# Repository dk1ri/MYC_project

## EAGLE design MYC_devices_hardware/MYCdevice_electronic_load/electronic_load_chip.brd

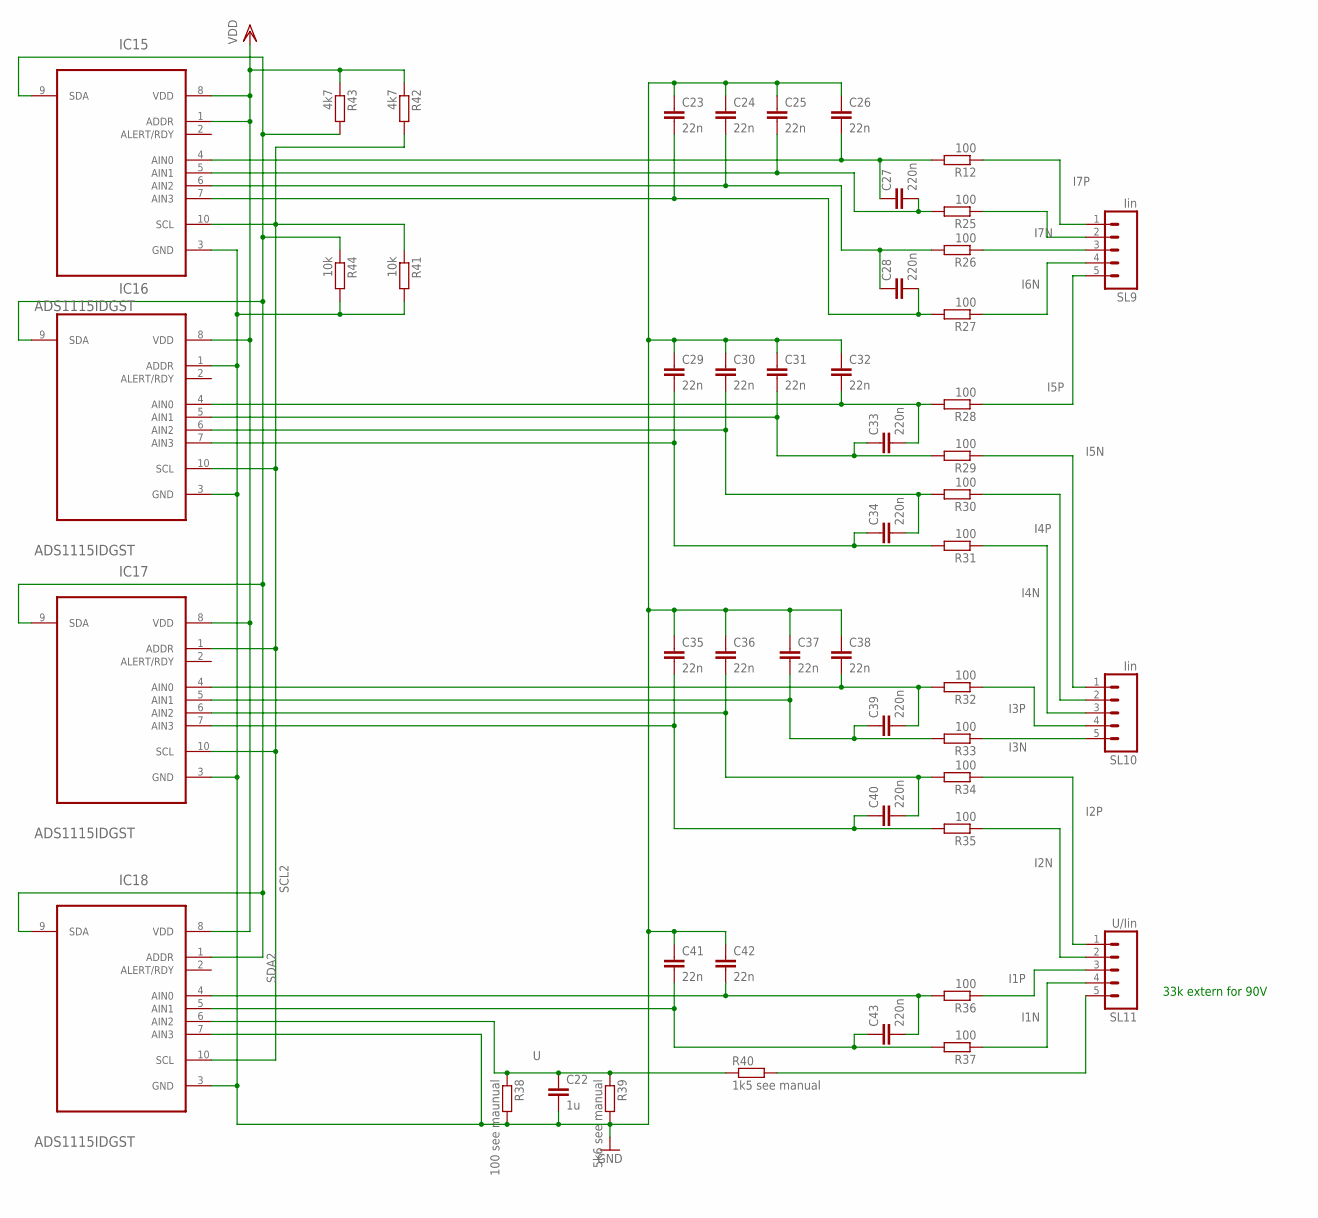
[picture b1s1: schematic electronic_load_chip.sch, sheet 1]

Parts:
C22: 1u; C1206
C23, C24, C25, C26, C29, C30, C31, C32, C35, C36, C37, C38, C41, C42: 22n; C1206
C27, C28, C33, C34, C39, C40, C43: 220n; C1206
IC15, IC16, IC17, IC18: ADS1115IDGST; SOP50P490X110-10N
R12, R25, R26, R27, R28, R29, R30, R31, R32, R33, R34, R35, R36, R37: 100; R1206
R38: 100 see maunual; R1206
R39: 5k6 see manual; R1206
R40: 1k5 see manual; R1206
R41, R44: 10k; R1206
R42, R43: 4k7; R1206
SL9, SL10: Iin; 05P
SL11: U/Iin; 05P

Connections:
GND: C22.2, C23.1, C24.1, C25.1, C26.1, C29.1, C30.1, C31.1, C32.1, C35.1, C36.1, C37.1, C38.1, C41.1, C42.1, IC15.3 (GND), IC16.1 (ADDR), IC16.3 (GND), IC17.3 (GND), IC18.3 (GND), IC18.7 (AIN3), R38.2, R39.2, R41.2, R44.2; also elsewhere on the board
I1N: R37.1, SL11.4
I1P: R36.1, SL11.3
I2N: R35.1, SL11.2
I2P: R34.1, SL11.1
I3N: R33.1, SL10.5
I3P: R32.1, SL10.4
I4N: R31.1, SL10.3
I4P: R30.1, SL10.2
I5N: R29.1, SL10.1
I5P: R28.1, SL9.5
I6N: R27.1, SL9.4
I6P: R26.1, SL9.3
I7N: R25.1, SL9.2
I7P: R12.1, SL9.1
unnamed: C26.2, C27.1, IC15.4 (AIN0), R12.2
unnamed: C32.2, C33.2, IC16.4 (AIN0), R28.2
unnamed: R40.2, SL11.5
unnamed: C31.2, C33.1, IC16.5 (AIN1), R29.2
unnamed: C30.2, C34.2, IC16.6 (AIN2), R30.2
unnamed: C29.2, C34.1, IC16.7 (AIN3), R31.2
unnamed: C38.2, C39.2, IC17.4 (AIN0), R32.2
unnamed: C37.2, C39.1, IC17.5 (AIN1), R33.2
unnamed: C36.2, C40.2, IC17.6 (AIN2), R34.2
unnamed: C24.2, C28.1, IC15.6 (AIN2), R26.2
unnamed: C25.2, C27.2, IC15.5 (AIN1), R25.2
unnamed: C35.2, C40.1, IC17.7 (AIN3), R35.2
unnamed: C23.2, C28.2, IC15.7 (AIN3), R27.2
unnamed: C42.2, C43.2, IC18.4 (AIN0), R36.2
unnamed: C41.2, C43.1, IC18.5 (AIN1), R37.2
SCL2: IC15.10 (SCL), IC16.10 (SCL), IC17.1 (ADDR), IC17.10 (SCL), IC18.10 (SCL), R41.1, R42.2; also elsewhere on the board
SDA2: IC15.9 (SDA), IC16.9 (SDA), IC17.9 (SDA), IC18.1 (ADDR), IC18.9 (SDA), R43.2, R44.1; also elsewhere on the board
U: C22.1, IC18.6 (AIN2), R38.1, R39.1, R40.1
VDD: IC15.1 (ADDR), IC15.8 (VDD), IC16.8 (VDD), IC17.8 (VDD), IC18.8 (VDD), R42.1, R43.1; also elsewhere on the board

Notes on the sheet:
33k extern for 90V

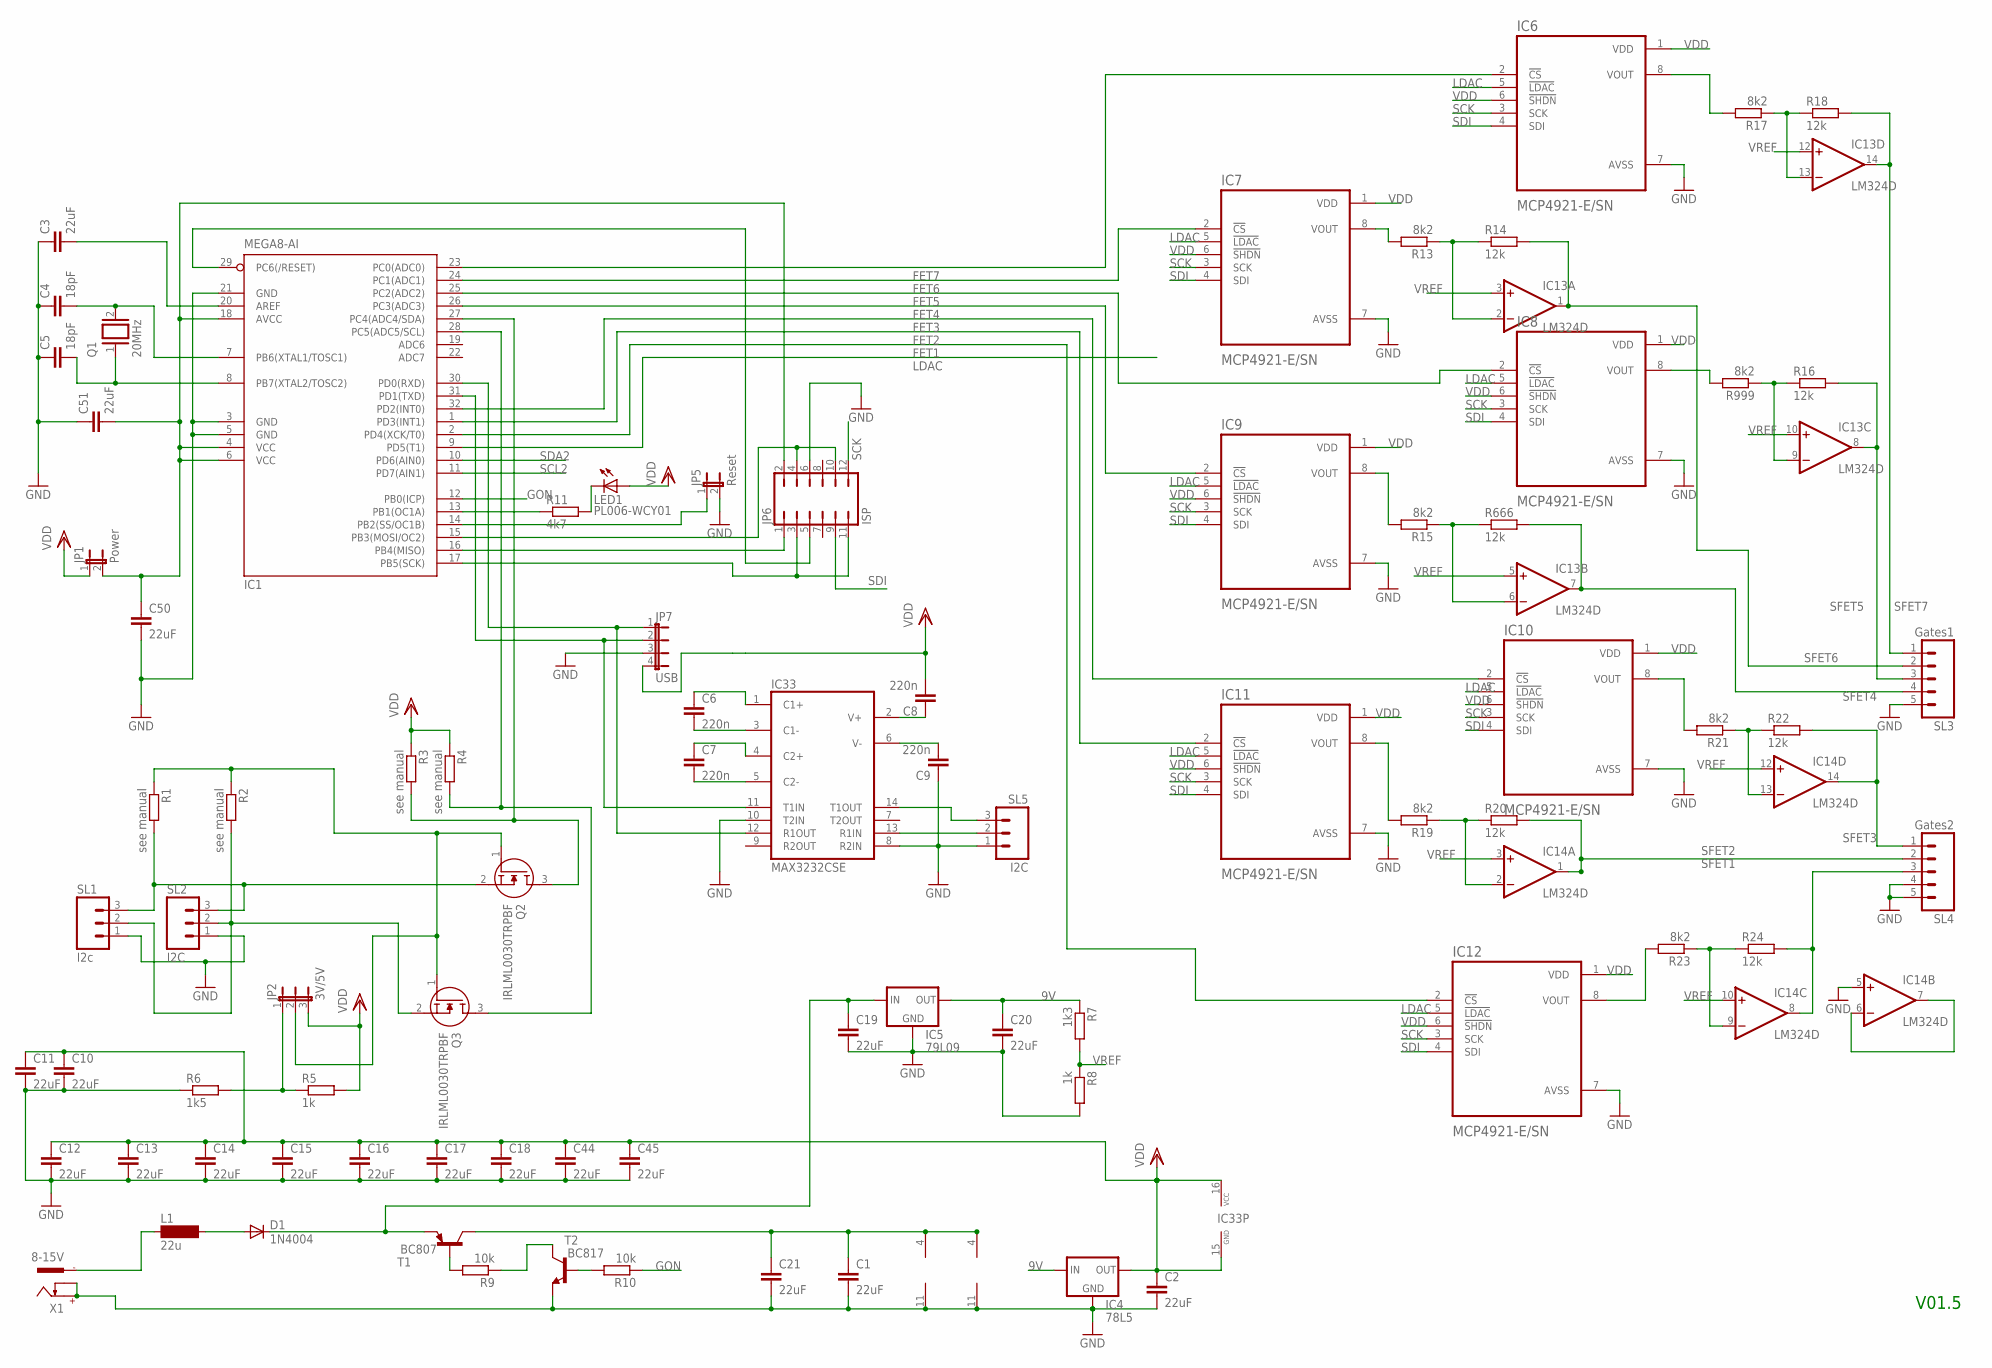
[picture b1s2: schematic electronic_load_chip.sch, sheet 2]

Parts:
C1, C2, C3, C10, C11, C12, C13, C14, C15, C16, C17, C18, C19, C20, C21, C44, C45, C50, C51: 22uF; C1206
C4, C5: 18pF; C025-025X050
C6, C7, C8, C9: 220n; C1206
D1: 1N4004; DO41-10
IC1: MEGA8-AI; TQFP32-08
IC4: 78L5; 78LXX
IC5: 79L09; 78LXX
IC6, IC7, IC8, IC9, IC10, IC11, IC12: MCP4921-E/SN; SOIC127P600X175-8N
IC13, IC14: LM324D; SO14
IC33: MAX3232CSE; SO16
JP1: Power; JP1
JP2: 3V/5V; JP2
JP5: Reset; JP1
JP6: ISP; JP6Q
JP7: USB; JP4
L1: 22u; MS85
LED1: PL006-WCY01; SOT23
Q1: 20MHz; QS
Q2, Q3: IRLML0030TRPBF; SOT95P237X112-3N
R1, R2, R3, R4: see manual; R1206
R5, R8: 1k; R1206
R6: 1k5; R1206
R7: 1k3; R1206
R9, R10: 10k; R1206
R11: 4k7; R1206
R13, R15, R17, R19, R21, R23, R999: 8k2; R1206
R14, R16, R18, R20, R22, R24, R666: 12k; R1206
SL1: I2c; 03P
SL2, SL5: I2C; 03P
SL3: Gates1; 05P
SL4: Gates2; 05P
T1: BC807; SOT23-BEC
T2: BC817; SOT23-BEC
X1: 8-15V; 737992-5

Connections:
9V: C20.1, IC4.IN, IC5.OUT, R7.1
C13: C6.1, IC33.1 (C1+)
FET1: IC1.2 (PD4(XCK/T0)), IC12.2 (!CS)
FET2: IC1.1 (PD3(INT1)), IC11.2 (!CS)
FET3: IC1.32 (PD2(INT0)), IC10.2 (!CS)
FET4: IC1.26 (PC3(ADC3)), IC9.2 (!CS)
FET5: IC1.25 (PC2(ADC2)), IC8.2 (!CS)
FET6: IC1.24 (PC1(ADC1)), IC7.2 (!CS)
FET7: IC1.23 (PC0(ADC0)), IC6.2 (!CS)
GND: C1.2, C2.2, C3.1, C4.1, C5.1, C9.1, C10.2, C11.2, C12.2, C13.2, C14.2, C15.2, C16.2, C17.2, C18.2, C19.2, C20.2, C21.2, C44.2, C45.2, C50.2, C51.1, IC1.3 (GND), IC1.5 (GND), IC1.21 (GND), IC4.GND, IC5.GND, IC6.7 (AVSS), IC7.7 (AVSS), IC8.7 (AVSS), IC9.7 (AVSS), IC10.7 (AVSS), IC11.7 (AVSS), IC12.7 (AVSS), IC13.11 (V-), IC14.5 (+IN), IC14.11 (V-), IC33.8 (R2IN), IC33.10 (T2IN), JP5.2, JP6.6, JP7.3, R6.1, R8.2, SL1.1, SL2.1, SL3.5, SL4.4, SL4.5, SL5.1, T2.E, X1.+, X1.K; also elsewhere on the board
GON: IC1.12 (PB0(ICP)), R10.1
LDAC: IC1.9 (PD5(T1)), IC6.5 (!LDAC), IC7.5 (!LDAC), IC8.5 (!LDAC), IC9.5 (!LDAC), IC10.5 (!LDAC), IC11.5 (!LDAC), IC12.5 (!LDAC)
unnamed: IC8.8 (VOUT), R999.2
unnamed: C7.2, IC33.5 (C2-)
unnamed: C50.1, C51.2, IC1.4 (VCC), IC1.6 (VCC), IC1.18 (AVCC), JP1.2, JP6.2
unnamed: Q2.2 (S), R1.2, SL1.3, SL2.3
unnamed: IC1.31 (PD1(TXD)), IC33.11 (T1IN), JP7.2
unnamed: L1.1, X1.-1
unnamed: IC33.13 (R1IN), SL5.2
unnamed: C5.2, IC1.8 (PB7(XTAL2/TOSC2)), Q1.1
unnamed: D1.A, L1.2
unnamed: C7.1, IC33.4 (C2+)
unnamed: C6.2, IC33.3 (C1-)
unnamed: IC1.16 (PB4(MISO)), JP6.1
unnamed: C8.1, IC33.2 (V+)
unnamed: C9.2, IC33.6 (V-)
unnamed: IC1.29 (PC6(/RESET)), JP6.5
unnamed: C4.2, IC1.7 (PB6(XTAL1/TOSC1)), Q1.2
unnamed: IC12.8 (VOUT), R23.2
unnamed: IC6.8 (VOUT), R17.2
unnamed: Q3.2 (S), R2.2, SL1.2, SL2.2
unnamed: IC1.15 (PB3(MOSI/OC2)), JP6.4, JP6.10
unnamed: IC11.8 (VOUT), R19.2
unnamed: IC7.8 (VOUT), R13.2
unnamed: IC33.14 (T1OUT), SL5.3
unnamed: IC1.27 (PC4(ADC4/SDA)), Q2.3 (D), R3.2
unnamed: IC13.13 (-IN), R17.1, R18.1
unnamed: IC1.14 (PB2(SS/OC1B)), JP5.1
unnamed: IC13.9 (-IN), R16.1, R999.1
unnamed: IC14.13 (-IN), R21.1, R22.1
unnamed: IC10.8 (VOUT), R21.2
unnamed: IC1.30 (PD0(RXD)), IC33.12 (R1OUT), JP7.1
unnamed: LED1.3 (C), R11.2
unnamed: IC1.17 (PB5(SCK)), JP6.3, JP6.11
unnamed: IC1.28 (PC5(ADC5/SCL)), Q3.3 (D), R4.2
unnamed: JP2.1, R5.1, R6.2
unnamed: IC9.8 (VOUT), R15.2
unnamed: IC1.13 (PB1(OC1A)), R11.1
unnamed: C19.1, D1.C, IC5.IN, T1.E
unnamed: IC14.2 (-IN), R19.1, R20.1
unnamed: IC14.9 (-IN), R23.1, R24.1
unnamed: C1.1, C21.1, IC13.4 (V+), IC14.4 (V+), T1.C
unnamed: C3.2, IC1.20 (AREF)
unnamed: R9.2, T1.B
unnamed: JP2.2, Q2.1 (G), Q3.1 (G), R1.1, R2.1
unnamed: R9.1, T2.C
unnamed: R10.2, T2.B
unnamed: IC13.6 (-IN), R15.1, R666.1
unnamed: IC13.2 (-IN), R13.1, R14.1
unnamed: IC14.6 (-IN), IC14.7 (OUT)
SCK: IC6.3 (SCK), IC7.3 (SCK), IC8.3 (SCK), IC9.3 (SCK), IC10.3 (SCK), IC11.3 (SCK), IC12.3 (SCK), JP6.12
SCL2: IC1.11 (PD7(AIN1)); also elsewhere on the board
SDA2: IC1.10 (PD6(AIN0)); also elsewhere on the board
SDI: IC6.4 (SDI), IC7.4 (SDI), IC8.4 (SDI), IC9.4 (SDI), IC10.4 (SDI), IC11.4 (SDI), IC12.4 (SDI), JP6.9
SFET1: IC14.8 (OUT), R24.2, SL4.3
SFET2: IC14.1 (OUT), R20.2, SL4.2
SFET3: IC14.14 (OUT), R22.2, SL4.1
SFET4: IC13.7 (OUT), R666.2, SL3.4
SFET5: IC13.8 (OUT), R16.2, SL3.3
SFET6: IC13.1 (OUT), R14.2, SL3.2
SFET7: IC13.14 (OUT), R18.2, SL3.1
VDD: C2.1, C8.2, C10.1, C11.1, C12.1, C13.1, C14.1, C15.1, C16.1, C17.1, C18.1, C44.1, C45.1, IC4.OUT, IC6.1 (VDD), IC6.6 (!SHDN), IC7.1 (VDD), IC7.6 (!SHDN), IC8.1 (VDD), IC8.6 (!SHDN), IC9.1 (VDD), IC9.6 (!SHDN), IC10.1 (VDD), IC10.6 (!SHDN), IC11.1 (VDD), IC11.6 (!SHDN), IC12.1 (VDD), IC12.6 (!SHDN), IC33.15 (GND), IC33.16 (VCC), JP1.1, JP2.3, JP7.4, LED1.1 (A), R3.1, R4.1, R5.2; also elsewhere on the board
VREF: IC13.3 (+IN), IC13.5 (+IN), IC13.10 (+IN), IC13.12 (+IN), IC14.3 (+IN), IC14.10 (+IN), IC14.12 (+IN), R7.2, R8.1

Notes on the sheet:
V01.5

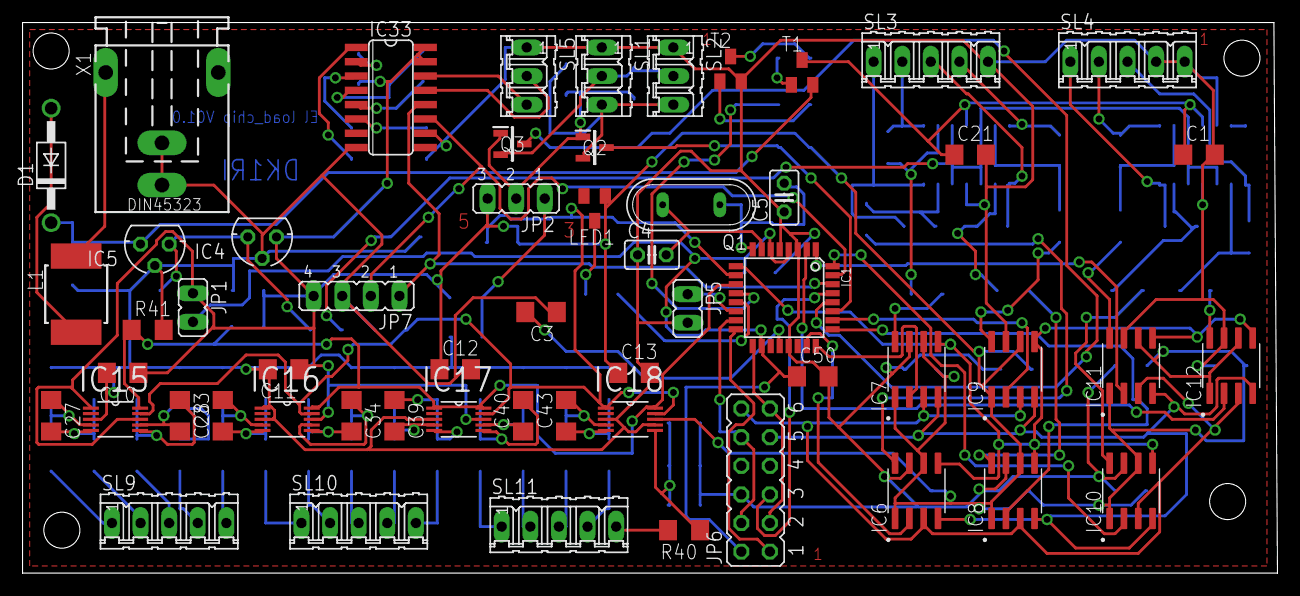
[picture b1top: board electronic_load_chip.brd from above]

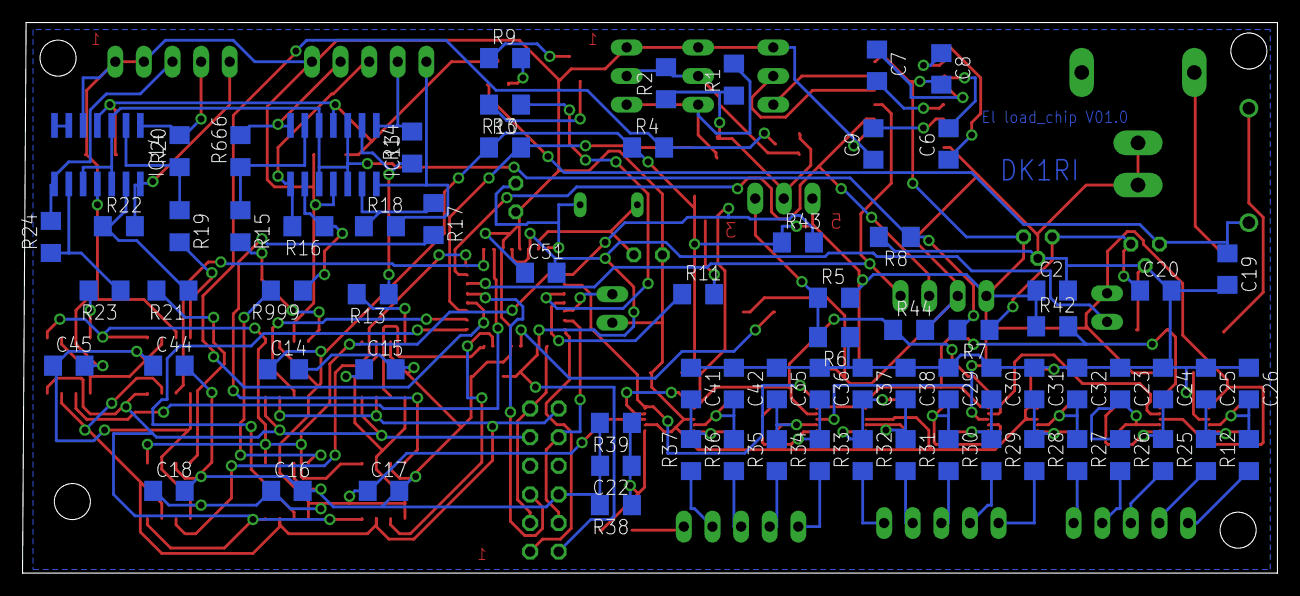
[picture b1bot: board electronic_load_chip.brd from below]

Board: 2 copper layers, 111.4 x 48.9 mm, 132 parts (76 on the bottom side), 103 nets.

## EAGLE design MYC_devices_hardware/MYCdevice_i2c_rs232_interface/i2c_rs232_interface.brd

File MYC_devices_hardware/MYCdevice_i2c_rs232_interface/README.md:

# I2C-RS232 Interface for MYC Systems

This is a device, which understand the MYC protocol.

The hardware can be used for a few other projects as well.

The software can be used as a templete for other MYC devices

For details of the MYC protocol see the docomentation or read www.dk1ri.de -> MYC

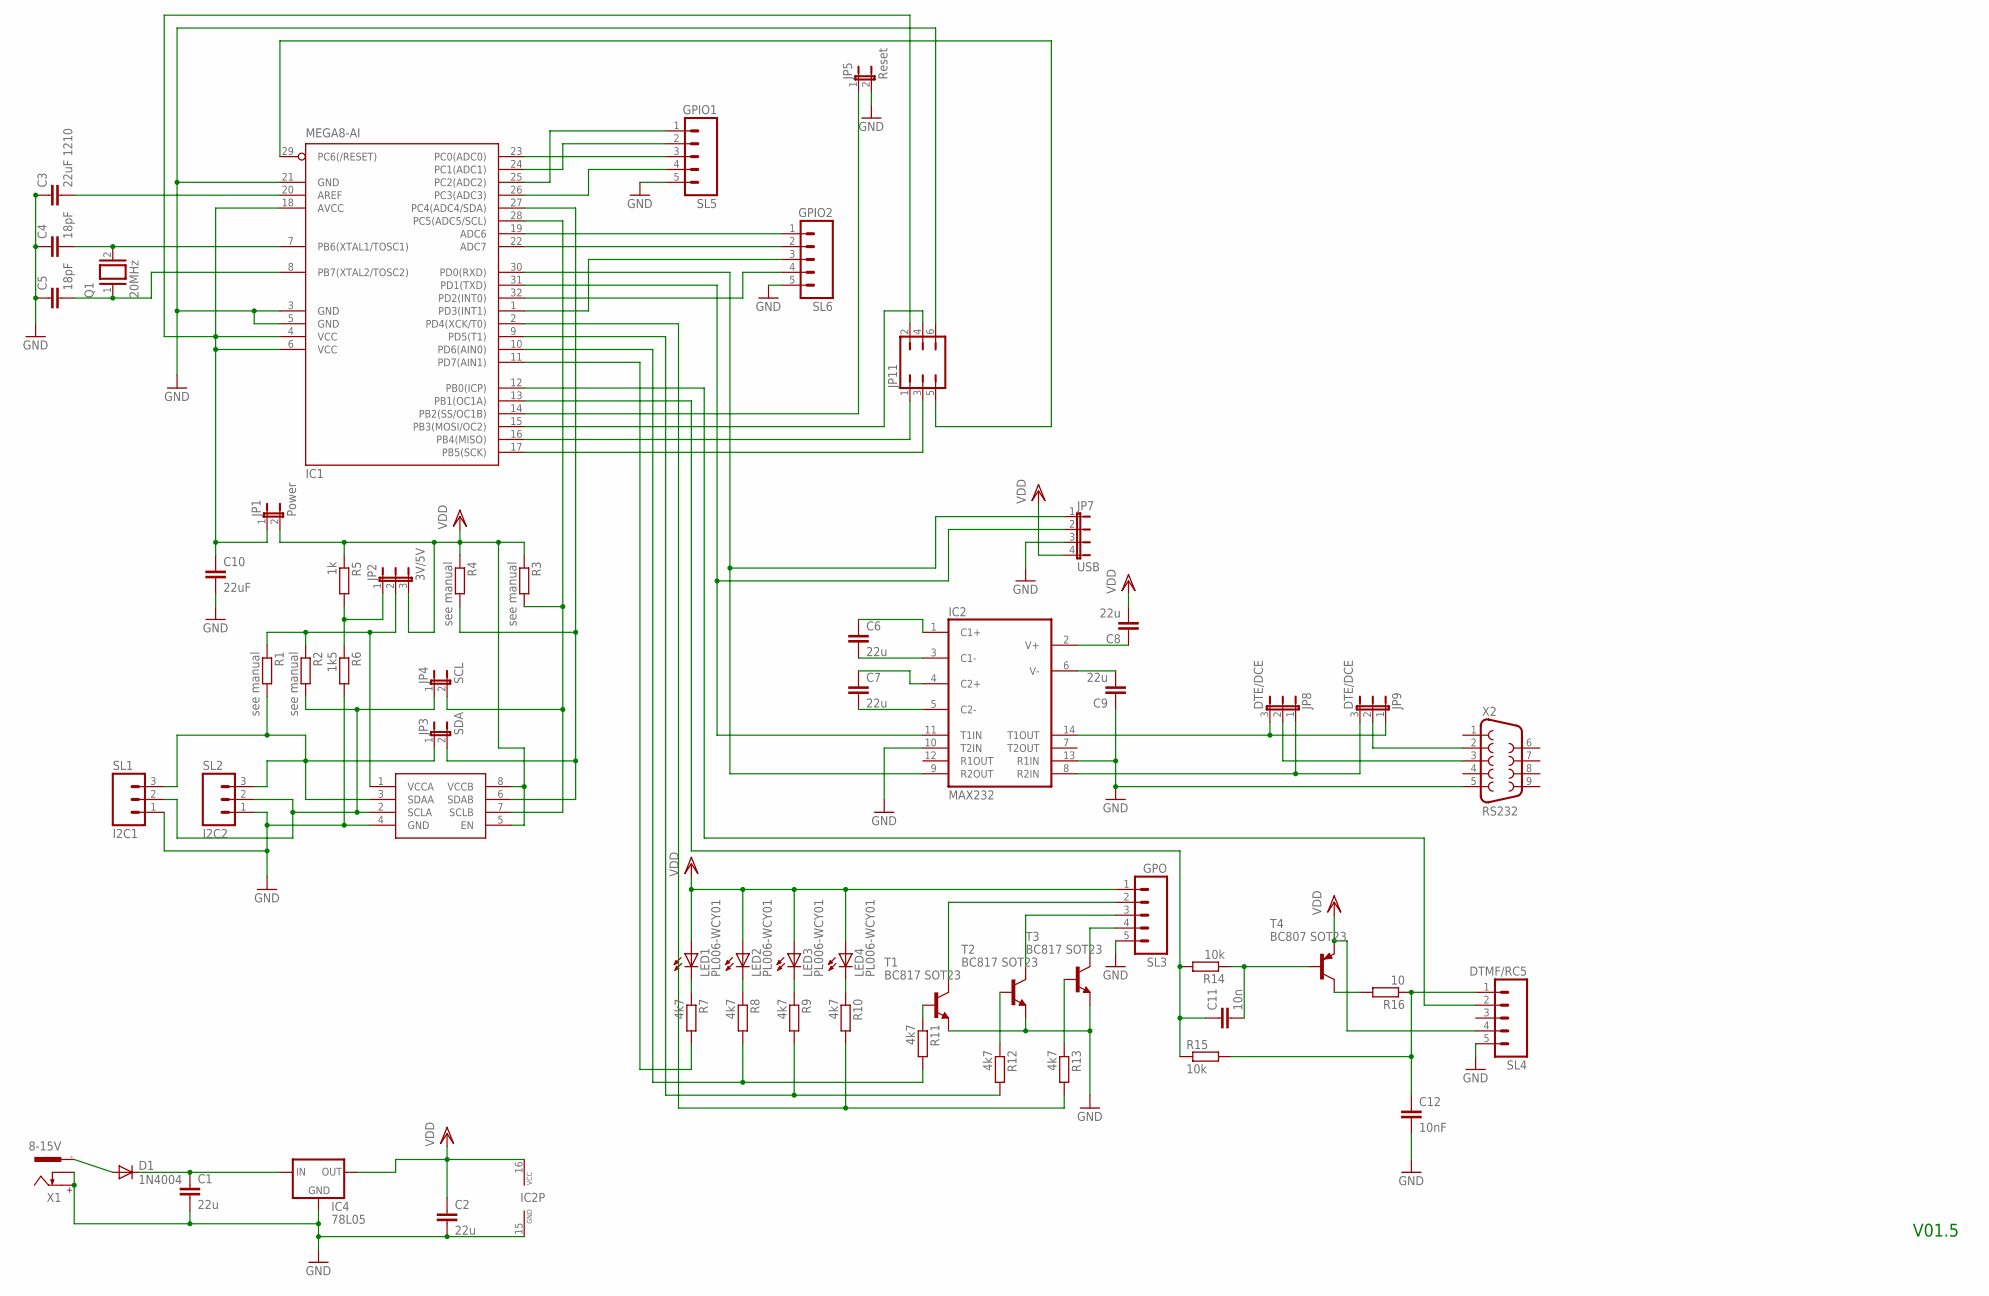
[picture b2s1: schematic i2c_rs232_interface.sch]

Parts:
C1, C2, C6, C7, C8, C9: 22u; C1206
C3: 22uF 1210; C1206
C4, C5: 18pF; C025-025X050
C10: 22uF; C1206
C11: 10n; C1206
C12: 10nF; C1206
D1: 1N4004; DO41-10
IC1: MEGA8-AI; TQFP32-08
IC2: MAX232; DIL16
IC3: PCA9517; SO-08
IC4: 78L05; 78LXX
JP1: Power; JP1
JP2: 3V/5V; JP2
JP3: SDA; JP1
JP4: SCL; JP1
JP5: Reset; JP1
JP7: USB; JP4
JP8, JP9: DTE/DCE; JP2
JP11: JP3Q
LED1, LED2, LED3, LED4: PL006-WCY01; SOT23
Q1: 20MHz; QS
R1, R2, R3, R4: see manual; R1206
R5: 1k; R1206
R6: 1k5; R1206
R7, R8, R9, R10, R11, R12, R13: 4k7; R1206
R14, R15: 10k; R1206
R16: 10; R1206
SL1: I2C1; 03P
SL2: I2C2; 03P
SL3: GPO; 05P
SL4: DTMF/RC5; 05P
SL5: GPIO1; 05P
SL6: GPIO2; 05P
T1, T2, T3: BC817 SOT23; SOT23-BEC
T4: BC807 SOT23; SOT23-BEC
X1: 8-15V; 737992-5
X2: RS232; F09H

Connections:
C13: C6.1, IC2.1 (C1+)
GND: C1.2, C2.2, C3.1, C4.1, C5.1, C9.1, C10.2, C12.2, IC1.3 (GND), IC1.5 (GND), IC1.21 (GND), IC2.10 (T2IN), IC2.13 (R1IN), IC2.15 (GND), IC3.4 (GND), IC4.GND, JP5.2, JP7.3, JP11.6, R6.2, SL1.1, SL2.1, SL3.5, SL4.5, SL5.5, SL6.5, T1.E, T2.E, T3.E, X1.+, X1.K, X2.5
unnamed: IC1.11 (PD7(AIN1)), R7.2
unnamed: IC1.30 (PD0(RXD)), IC2.9 (R2OUT), JP7.1
unnamed: C7.2, IC2.5 (C2-)
unnamed: JP9.2, X2.2
unnamed: IC1.27 (PC4(ADC4/SDA)), IC3.6 (SDAB), JP3.2, R4.2
unnamed: IC1.14 (PB2(SS/OC1B)), JP5.1
unnamed: IC1.25 (PC2(ADC2)), SL5.1
unnamed: R11.1, T1.B
unnamed: JP8.2, X2.3
unnamed: IC2.14 (T1OUT), JP8.3, JP9.1
unnamed: C10.1, IC1.4 (VCC), IC1.6 (VCC), IC1.18 (AVCC), JP1.1, JP11.2
unnamed: IC1.31 (PD1(TXD)), IC2.11 (T1IN), JP7.2
unnamed: C7.1, IC2.4 (C2+)
unnamed: C6.2, IC2.3 (C1-)
unnamed: IC1.16 (PB4(MISO)), JP11.1
unnamed: C8.1, IC2.2 (V+)
unnamed: C9.2, IC2.6 (V-)
unnamed: IC1.29 (PC6(/RESET)), JP11.5
unnamed: C4.2, IC1.7 (PB6(XTAL1/TOSC1)), Q1.2
unnamed: IC1.17 (PB5(SCK)), JP11.3
unnamed: IC1.19 (ADC6), SL6.1
unnamed: IC1.28 (PC5(ADC5/SCL)), IC3.7 (SCLB), JP4.2, R3.2
unnamed: IC1.10 (PD6(AIN0)), R8.2, R11.2
unnamed: R13.1, T3.B
unnamed: IC1.9 (PD5(T1)), R9.2, R12.2
unnamed: IC1.23 (PC0(ADC0)), SL5.3
unnamed: D1.A, X1.-1
unnamed: IC1.15 (PB3(MOSI/OC2)), JP11.4
unnamed: C11.2, R14.1, T4.B
unnamed: C11.1, IC1.13 (PB1(OC1A)), R14.2, R15.1
unnamed: R16.2, T4.C
unnamed: C12.1, R15.2, R16.1, SL4.1
unnamed: C1.1, D1.C, IC4.IN
unnamed: R12.1, T2.B
unnamed: C3.2, IC1.20 (AREF)
unnamed: IC1.24 (PC1(ADC1)), SL5.2
unnamed: C5.2, IC1.8 (PB7(XTAL2/TOSC2)), Q1.1
unnamed: IC3.2 (SCLA), JP4.1, R2.2, SL1.2, SL2.2
unnamed: IC1.26 (PC3(ADC3)), SL5.4
unnamed: IC1.1 (PD3(INT1)), SL6.3
unnamed: IC2.8 (R2IN), JP8.1, JP9.3
unnamed: IC1.12 (PB0(ICP)), SL4.2
unnamed: LED4.3 (C), R10.1
unnamed: IC3.3 (SDAA), JP3.1, R1.2, SL1.3, SL2.3
unnamed: SL3.2, T1.C
unnamed: SL3.3, T2.C
unnamed: SL3.4, T3.C
unnamed: LED3.3 (C), R9.1
unnamed: LED2.3 (C), R8.1
unnamed: LED1.3 (C), R7.1
unnamed: IC1.32 (PD2(INT0)), SL6.4
unnamed: IC1.2 (PD4(XCK/T0)), R10.2, R13.2
unnamed: JP2.1, R5.2, R6.1
unnamed: IC1.22 (ADC7), SL6.2
unnamed: IC3.1 (VCCA), JP2.2, R1.1, R2.1
VDD: C2.1, C8.2, IC2.16 (VCC), IC3.5 (EN), IC3.8 (VCCB), IC4.OUT, JP1.2, JP2.3, JP7.4, LED1.1 (A), LED2.1 (A), LED3.1 (A), LED4.1 (A), R3.1, R4.1, R5.1, SL3.1, SL4.4, T4.E

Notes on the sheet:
V01.5

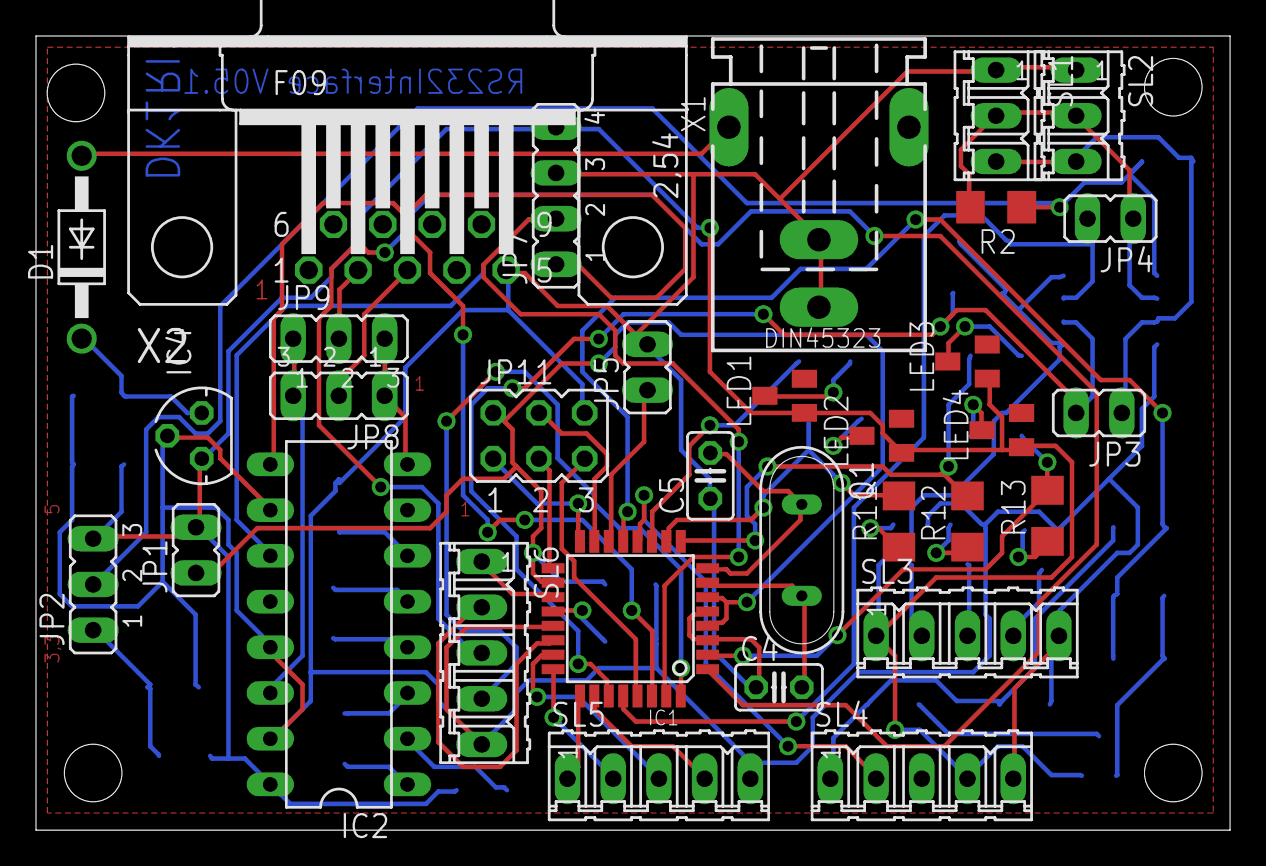
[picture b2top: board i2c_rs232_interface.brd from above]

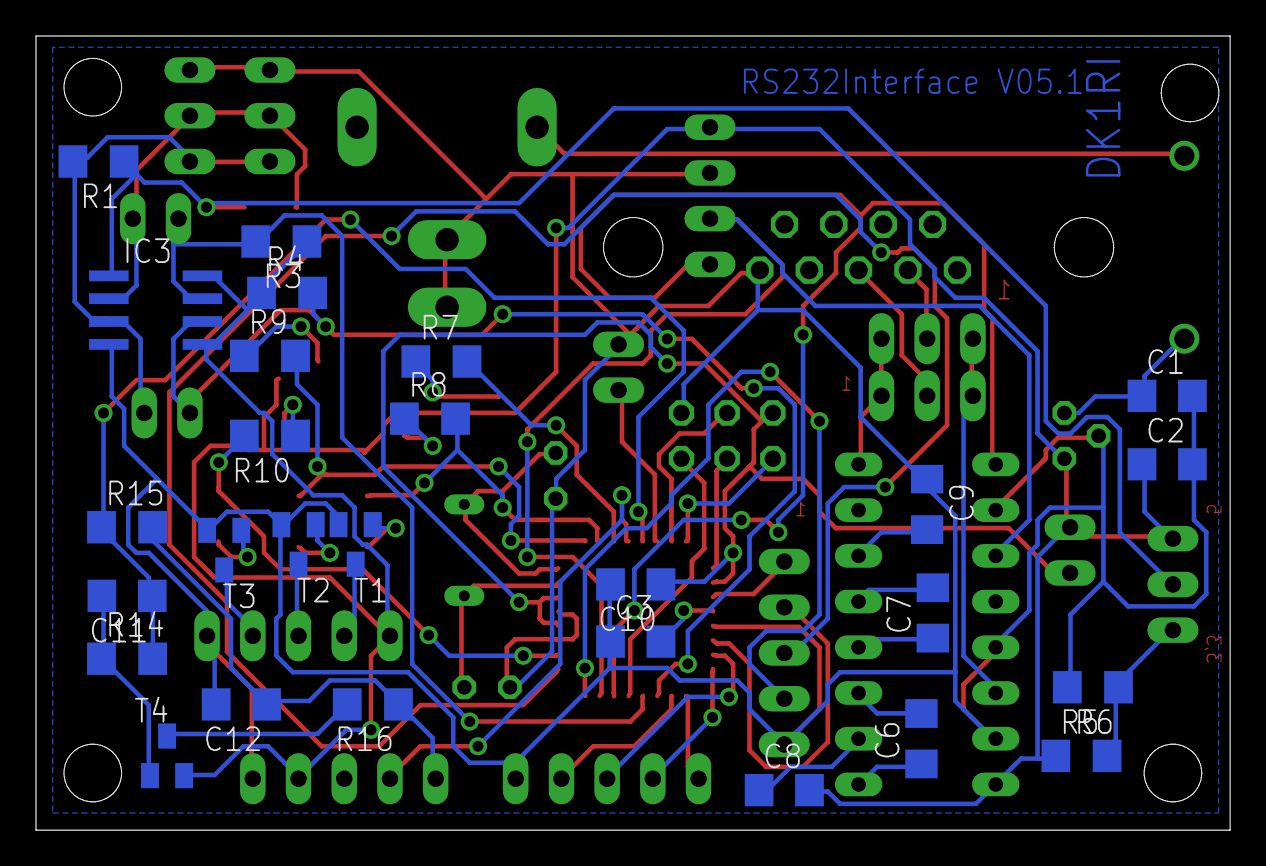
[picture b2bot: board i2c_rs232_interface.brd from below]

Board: 2 copper layers, 66.3 x 44.1 mm, 59 parts (27 on the bottom side), 58 nets.

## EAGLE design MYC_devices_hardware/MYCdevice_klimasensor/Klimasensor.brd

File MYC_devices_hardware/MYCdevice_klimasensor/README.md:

# MYC climatic sensor  with BME280

This is a sensor for temperature, humidity and pressure. 
The device is controlled by the MYC protocol.

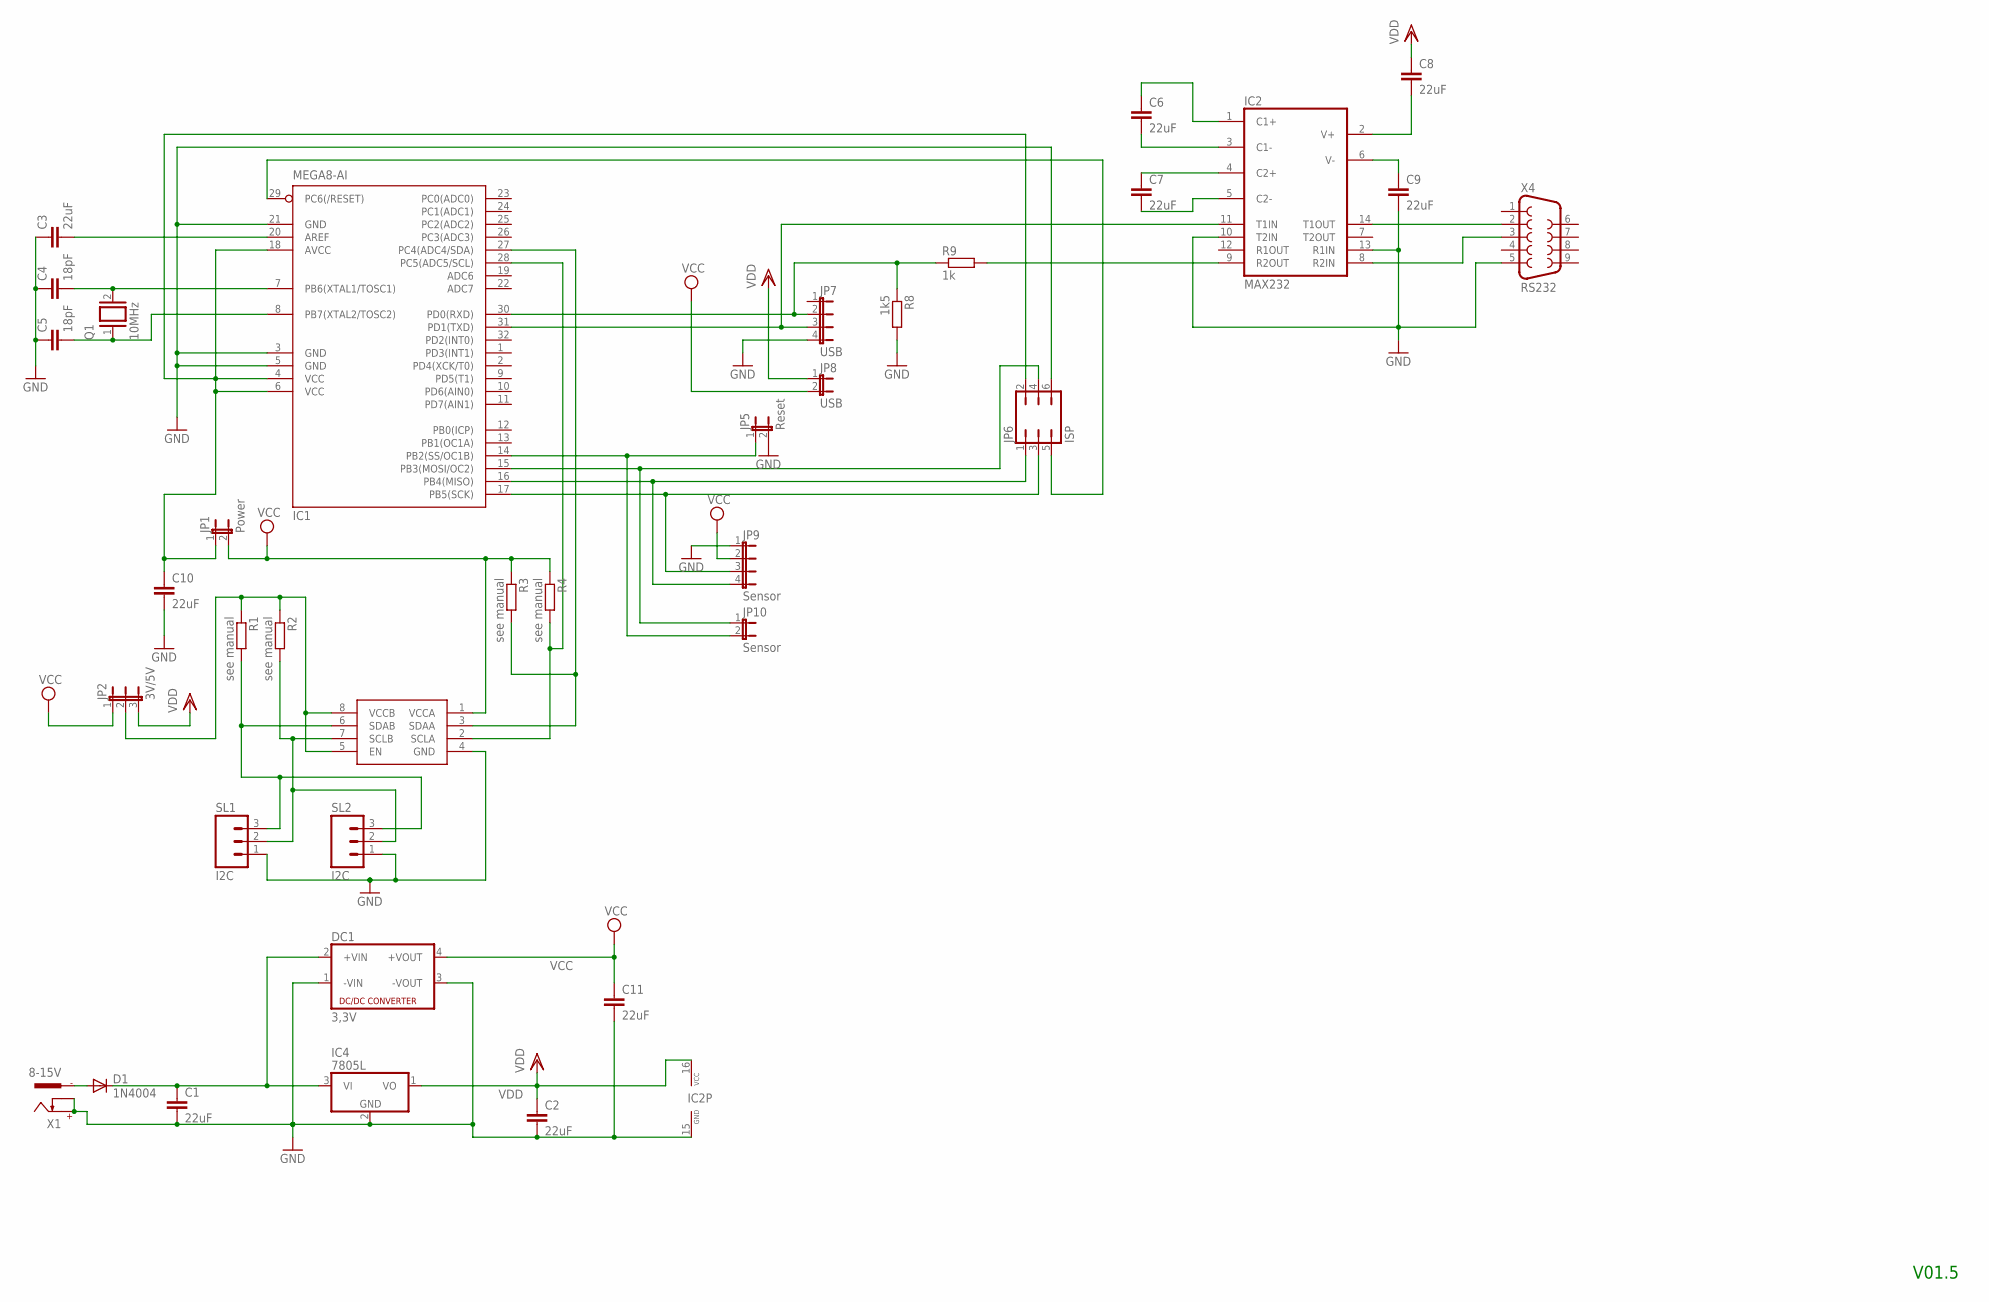
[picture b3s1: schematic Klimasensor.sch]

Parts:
C1, C2, C3, C6, C7, C8, C9, C10, C11: 22uF; C1206
C4, C5: 18pF; C025-025X050
D1: 1N4004; DO41-10
DC1: 3,3V; NME
IC1: MEGA8-AI; TQFP32-08
IC2: MAX232; DIL16
IC3: PCA9517; SO-08
IC4: 7805L; TO92
JP1: Power; JP1
JP2: 3V/5V; JP2
JP5: Reset; JP1
JP6: ISP; JP3Q
JP7: USB; JP4
JP8: USB; JP1
JP9: Sensor; JP4
JP10: Sensor; JP1
Q1: 10MHz; QS
R1, R2, R3, R4: see manual; R1206
R8: 1k5; R1206
R9: 1k; R1206
SL1, SL2: I2C; 03P
X1: 8-15V; 737992-5
X4: RS232; F09H

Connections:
GND: C1.2, C2.2, C3.1, C4.1, C5.1, C9.2, C10.2, C11.2, DC1.1 (-VIN), DC1.3 (-VOUT), IC1.3 (GND), IC1.5 (GND), IC1.21 (GND), IC2.10 (T2IN), IC2.13 (R1IN), IC2.15 (GND), IC3.4 (GND), IC4.2 (GND), JP5.2, JP6.6, JP7.4, JP9.1, R8.2, SL1.1, SL2.1, X1.+, X1.K, X4.5
unnamed: IC3.6 (SDAB), R1.2, SL1.3, SL2.3
unnamed: IC1.15 (PB3(MOSI/OC2)), JP6.4, JP10.1
unnamed: C1.1, D1.C, DC1.2 (+VIN), IC4.3 (VI)
unnamed: IC1.27 (PC4(ADC4/SDA)), IC3.3 (SDAA), R3.2
unnamed: IC3.5 (EN), IC3.8 (VCCB), JP2.2, R1.1, R2.1
unnamed: IC1.28 (PC5(ADC5/SCL)), IC3.2 (SCLA), R4.2
unnamed: IC1.17 (PB5(SCK)), JP6.3, JP9.3
unnamed: IC1.31 (PD1(TXD)), IC2.11 (T1IN), JP7.3
unnamed: IC1.14 (PB2(SS/OC1B)), JP5.1, JP10.2
unnamed: IC2.8 (R2IN), X4.3
unnamed: C3.2, IC1.20 (AREF)
unnamed: IC2.14 (T1OUT), X4.2
unnamed: IC1.16 (PB4(MISO)), JP6.1, JP9.4
unnamed: C8.2, IC2.2 (V+)
unnamed: C6.1, IC2.1 (C1+)
unnamed: IC1.29 (PC6(/RESET)), JP6.5
unnamed: C4.2, IC1.7 (PB6(XTAL1/TOSC1)), Q1.2
unnamed: C6.2, IC2.3 (C1-)
unnamed: C7.2, IC2.5 (C2-)
unnamed: IC3.7 (SCLB), R2.2, SL1.2, SL2.2
unnamed: C7.1, IC2.4 (C2+)
unnamed: C9.1, IC2.6 (V-)
unnamed: IC2.9 (R2OUT), R9.2
unnamed: C10.1, IC1.4 (VCC), IC1.6 (VCC), IC1.18 (AVCC), JP1.1, JP6.2
unnamed: D1.A, X1.-1
unnamed: IC1.30 (PD0(RXD)), JP7.2, R8.1, R9.1
unnamed: C5.2, IC1.8 (PB7(XTAL2/TOSC2)), Q1.1
VCC: C11.1, DC1.4 (+VOUT), IC3.1 (VCCA), JP1.2, JP2.1, JP8.2, JP9.2, R3.1, R4.1
VDD: C2.1, C8.1, IC2.16 (VCC), IC4.1 (VO), JP2.3, JP8.1

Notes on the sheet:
V01.5
